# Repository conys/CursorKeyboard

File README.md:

# CursorKeyboard
HHKB pro2で矢印だけを使うシーンにおいての利便性の向上を図るため，
矢印キーだけのキーボードを設計した．

ディレクトリ構成
- /arduino  : pro micro用スケッチ
- /drawing  : キースイッチ固定プレートと底板の図面
- /mykeyboard  : PCBのkicadプロジェクト

回路図
[schema](https://github.com/conys/CursorKeyboard/blob/image/images/schematic.pdf)

# Licence
This software is released under the MIT License, see LICENSE.

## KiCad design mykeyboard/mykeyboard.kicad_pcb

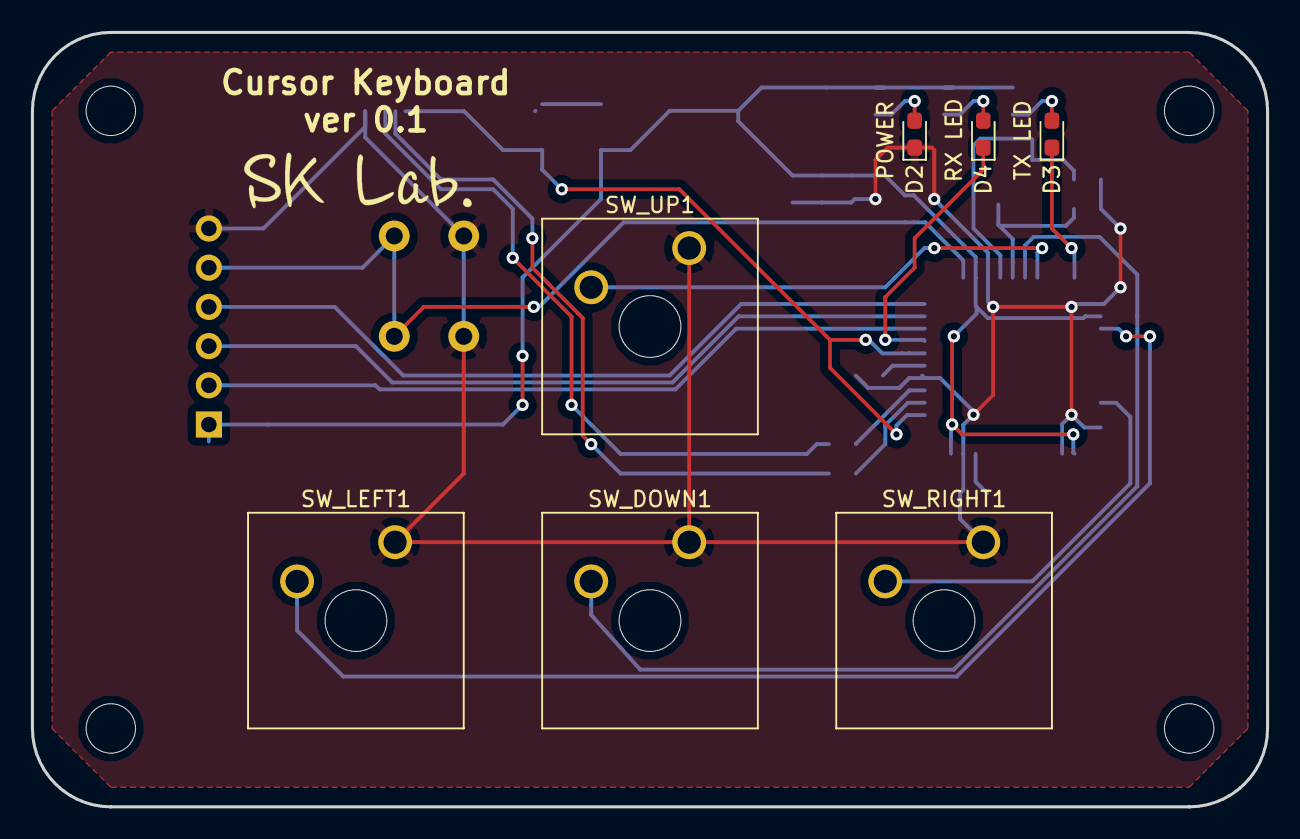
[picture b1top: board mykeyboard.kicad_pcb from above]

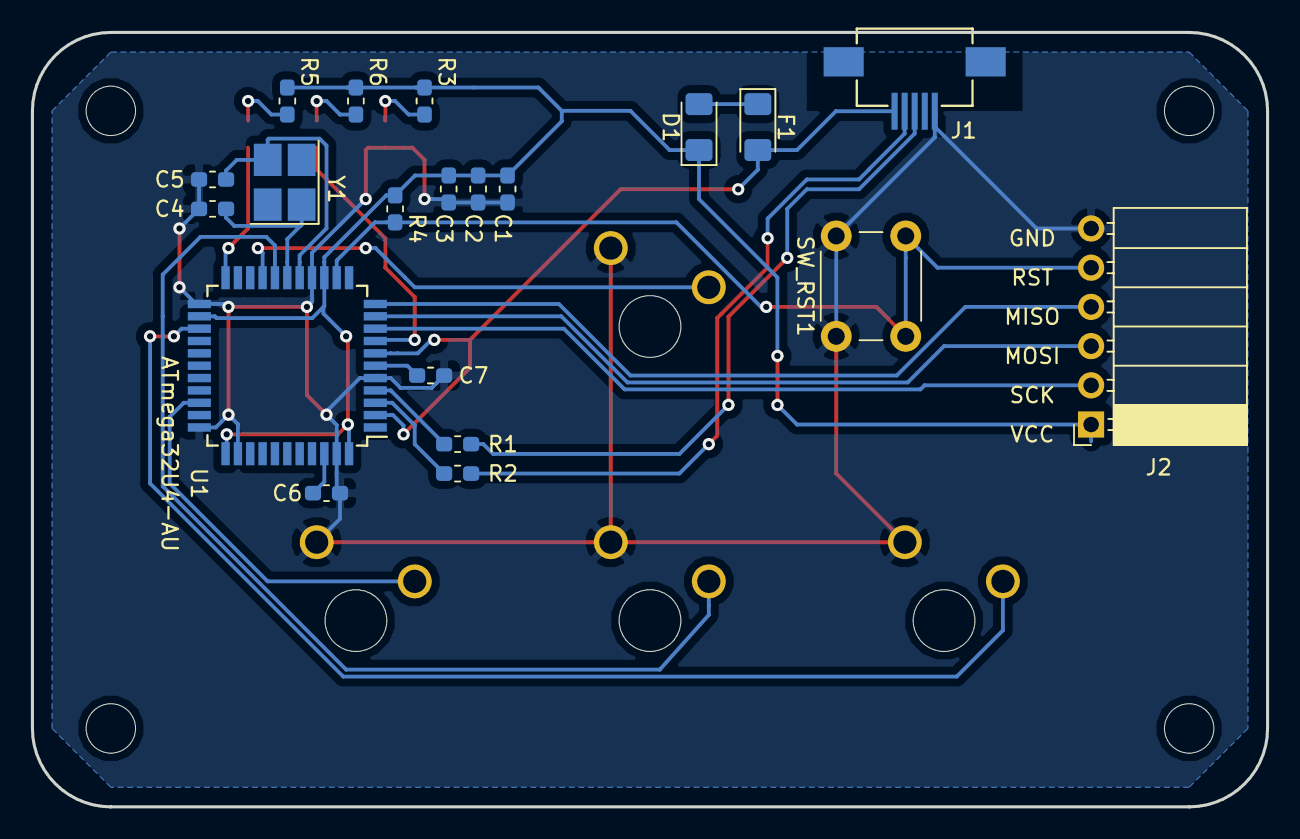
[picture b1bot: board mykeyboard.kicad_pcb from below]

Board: 2 copper layers, 80.0 x 50.2 mm, 27 parts (20 on the bottom side), 25 nets.

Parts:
C1: 10uF; C_0603_1608Metric_Pad1.05x0.95mm_HandSolder
C2, C7: 1uF; C_0603_1608Metric_Pad1.05x0.95mm_HandSolder
C3, C6: 0.1uF; C_0603_1608Metric_Pad1.05x0.95mm_HandSolder
C4, C5: 22pF; C_0603_1608Metric_Pad1.05x0.95mm_HandSolder
D1: D_Schottky; D_1206_3216Metric_Pad1.42x1.75mm_HandSolder
D2, D3, D4: LED; LED_0603_1608Metric_Pad1.05x0.95mm_HandSolder
F1: Polyfuse; D_1206_3216Metric_Pad1.42x1.75mm_HandSolder
J1: USB_B_Micro; USB_B_Micro_hirose_reverse
J2: Conn_01x06; PinSocket_1x06_P2.54mm_Horizontal
R1, R2: 22; R_0603_1608Metric_Pad1.05x0.95mm_HandSolder
R3, R5, R6: 1k; R_0603_1608Metric_Pad1.05x0.95mm_HandSolder
R4: 10k; R_0603_1608Metric_Pad1.05x0.95mm_HandSolder
SW_DOWN1: SW_Push; SW_Cherry_MX1A_1.00u_Plate
SW_LEFT1: SW_Push; SW_Cherry_MX1A_1.00u_Plate
SW_RIGHT1: SW_Push; SW_Cherry_MX1A_1.00u_Plate
SW_RST1: SW_Push; SW_PUSH_6mm
SW_UP1: SW_Push; SW_Cherry_MX1A_1.00u_Plate
U1: ATmega32U4-AU; TQFP-44_10x10mm_P0.8mm
Y1: 16MHz; Crystal_SMD_SeikoEpson_FA238-4Pin_3.2x2.5mm_HandSoldering

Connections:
/D2: SW_UP1.2, U1.19
/D3: SW_DOWN1.2, U1.18
/D4: SW_LEFT1.2, U1.25
/D5: SW_RIGHT1.2, U1.31
/D+: R1.2, U1.4
/D-: R2.2, U1.3
/MISO: J2.4, U1.11
/MOSI: J2.3, U1.10
/RST: J2.5, R4.2, SW_RST1.2, U1.13
/SCK: J2.2, U1.9
/UVCC: F1.2, J1.1, U1.2, U1.7
/VCC: C1.1, C2.1, C3.1, D1.1, J2.1, R3.1, R4.1, R5.1, R6.1, U1.14, U1.24, U1.34, U1.44
GND: C1.2, C2.2, C3.2, C4.2, C5.2, C6.2, C7.2, D2.1, J1.5, J2.6, SW_DOWN1.1, SW_LEFT1.1, SW_RIGHT1.1, SW_RST1.1, SW_UP1.1, U1.5, U1.15, U1.23, U1.33, U1.35, U1.43
unnamed: C4.1, U1.17, Y1.1
unnamed: C5.1, U1.16, Y1.2
unnamed: C6.1, U1.42
unnamed: C7.1, U1.6
unnamed: D1.2, F1.1
unnamed: D2.2, R3.2
unnamed: D3.1, U1.22
unnamed: D3.2, R5.2
unnamed: D4.1, U1.8
unnamed: D4.2, R6.2
unnamed: J1.2, R2.1
unnamed: J1.3, R1.1

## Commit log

2019-02-11 ver 0.1
2019-02-11 Added images
2019-02-11 Add images for README
2019-02-11 added schematic image
2019-02-11 added README.md
2019-02-11 readme
